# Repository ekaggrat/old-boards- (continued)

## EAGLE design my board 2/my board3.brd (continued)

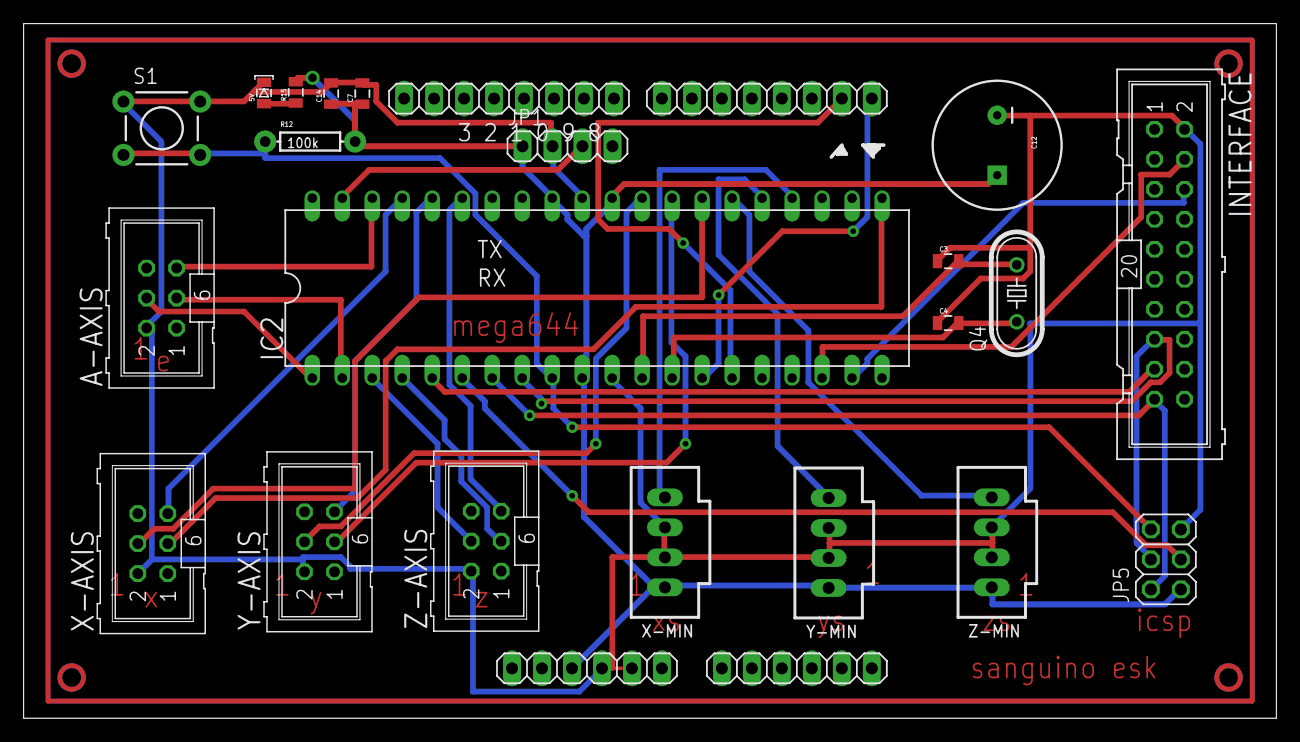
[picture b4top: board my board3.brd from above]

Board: 2 copper layers, 106.1 x 58.8 mm, 25 parts (0 on the bottom side), 30 nets.

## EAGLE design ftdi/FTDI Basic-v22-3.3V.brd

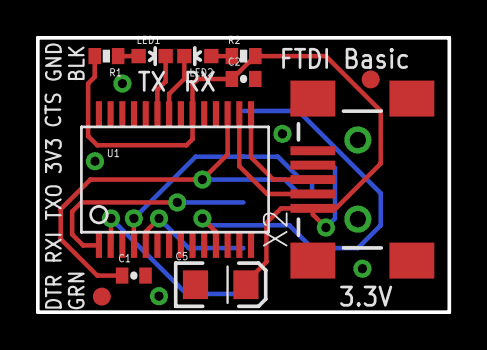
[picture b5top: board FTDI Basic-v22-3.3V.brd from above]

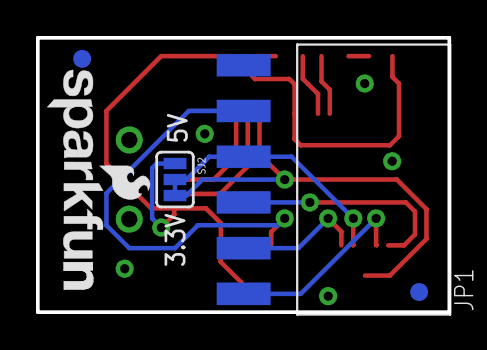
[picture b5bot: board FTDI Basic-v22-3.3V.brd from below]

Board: 2 copper layers, 22.9 x 15.2 mm, 17 parts (6 on the bottom side), 14 nets.

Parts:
C1, C2: 0.1uF; 0402-CAP
C5: 10uF; EIA3216
JP1: 1X06-SMD-FEMALE-V2
JP2: LOGO-SFESK; SFE-LOGO-FLAME
JP3, JP4, JP5, JP6: FIDUCIAL1X2; FIDUCIAL-1X2
LED1: Red; LED-0603
LED2: Green; LED-0603
R1, R2: 1K; 0402-RES
SJ2: SJ_3
U1: FT232RLSSOP; SSOP28DB
U$2: LOGO-SFENW2; SFE-NEW-WEB
X2: USB-SMD-NS; USB-MINIB-NOSTOP

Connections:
3.3V: C1.1, SJ2.3, U1.17
5V: C2.1, C5.A, R1.2, R2.2, SJ2.1, U1.20, X2.VBUS
CTS: JP1.2, U1.11
DTR: JP1.6, U1.2
GND: C1.2, C2.2, C5.C, JP1.1, U1.7, U1.18, U1.21, U1.25, U1.26, X2.GND
unnamed: LED1.A, R1.1
unnamed: LED2.A, R2.1
POWER: JP1.3, SJ2.2, U1.4
RXI: JP1.5, U1.5
RXLED: LED2.C, U1.22
TXLED: LED1.C, U1.23
TXO: JP1.4, U1.1
USB_D+: U1.15, X2.D+
USB_D-: U1.16, X2.D-

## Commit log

2023-12-20 all boards upload
